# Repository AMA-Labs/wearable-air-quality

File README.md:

# Wearable Air Quality Monitor
The device is based around the Arduino Nicla Sense ME  and incorporates aditional sensors to collect information on VOCs, CO2, Temperature, Humidity, and particulates. The objective is to provide a relatively low cost open design to monitor pollutants of concern.

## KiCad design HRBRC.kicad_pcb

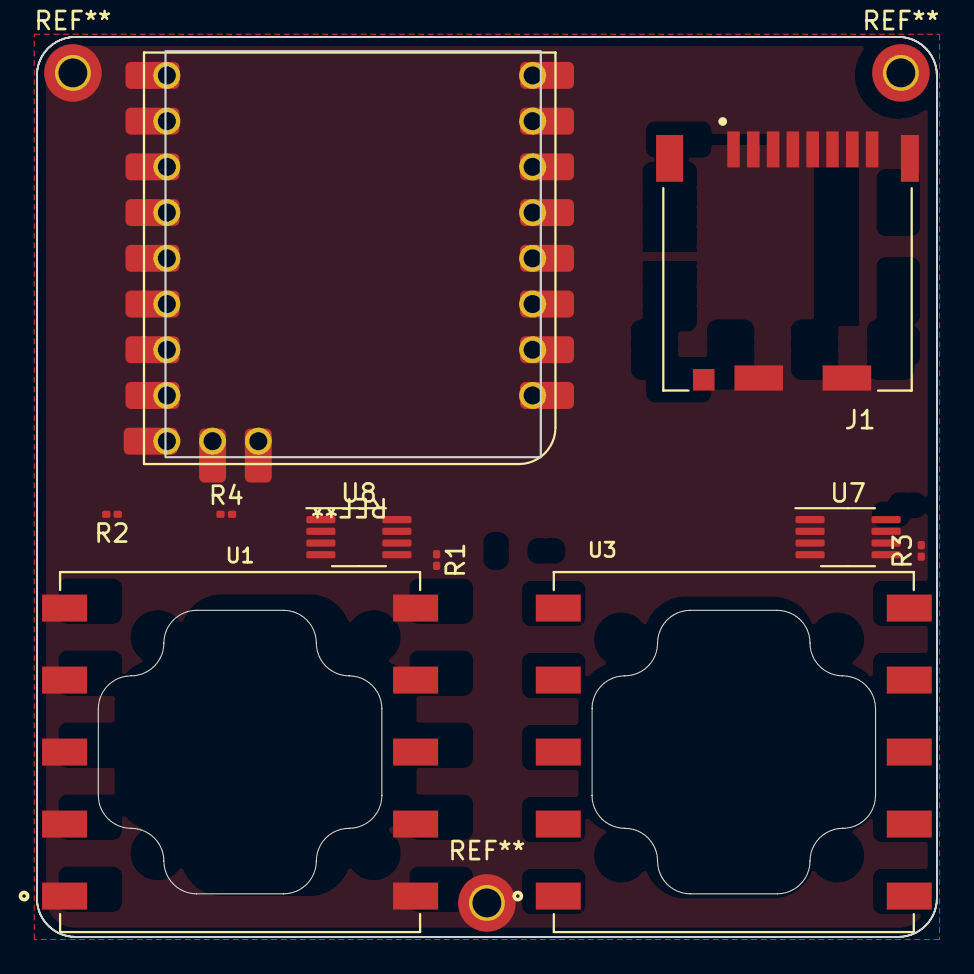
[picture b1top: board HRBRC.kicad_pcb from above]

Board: 2 copper layers, 50.0 x 50.0 mm, 10 parts (1 on the bottom side), 11 nets, no tracks yet.

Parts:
J1: Micro_SD_Card_Det_Hirose_DM3CS; HRS_DM3CS-SF
R1, R3: 49.9; R_0201_0603Metric
R2, R4: 499K; R_0201_0603Metric
U1, U3: 110-407; XDCR_110-407
U6: SCD41; SCD4x
U7, U8: MCP6L02x-xMS; MSOP-8_3x3mm_P0.65mm

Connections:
+3.3VA: U7.8 (V+), U8.8 (V+)
+3V3: J1.4 (VDD), U6.7 (VDD), U6.19 (VDDH)
GND: U6.6 (GND), U6.20 (GND), U6.21 (GND), U7.4 (V-), U8.4 (V-)
unnamed: U8.1, U8.5 (+)
unnamed: J1.6 (VSS), J1.9 (DET_B)
unnamed: R1.1, U1.6 (COUNTER)
unnamed: R3.1, U3.6 (COUNTER)
unnamed: U7.6 (-), U7.7
unnamed: U1.1 (WORKING), U1.10 (WORKING)
unnamed: U3.1 (WORKING), U3.10 (WORKING)
VGAS: U8.6 (-), U8.7

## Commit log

2022-11-23 Filled out README.md
2022-11-29 Added previous Kicad project
2023-04-18 Version 1.0 - Print raw values from sensors to TFT
2023-04-18 Arduino Libraries
2023-04-26 Comments reflecting necessary library changes
2023-05-18 Version2 - Optimized
